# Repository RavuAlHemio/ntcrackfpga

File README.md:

# ntcrackfpga

FPGA-based NT hash cracker.

NT hashes are universally `MD4(UTF16LE(password))`. If you think this sounds like low-hanging fruit, that's because it is.

The reference implementation runs on a Lattice ECP5 Evaluation Board (`LFE5UM5G-85F-EVN`) while tests are simulated using Icarus Verilog. However, the Verilog code should be generic enough to work anywhere; device-specific settings are limited to `src/ntcrackfpga.lpf` and `src/clockdiv.v`.

See `PROTOCOL.md` on how to communicate with the cracker.

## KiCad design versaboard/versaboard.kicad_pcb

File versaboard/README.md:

# Versa Board

The cracker itself is structured to run on a Lattice ECP5 Evaluation Board (`LFE5UM5G-85F-EVN`; relevant settings may be found in `src/ntcrackfpga.lpf` and `src/clockdiv.v`). To provide a more convenient interface without attempting to implement I2C or UART in Verilog (and failing miserably), a Microchip-SAM-based _Versa Board_ solution is implemented, which is meant to mate directly with the Versa pins on the evaluation board.

The centerpoint of the _Versa Board_ is a Microchip (ex-Atmel) SAML21G18 microcontroller.

A KiCad hardware design is provided in this directory; the software implementation (in Rust) is in the `software` subdirectory.

## SAML21 pinout

The following SAML21 pins are used for the interconnection with the evaluation board:

| SAML21 pin | ECP5 Eval Board | function           | direction | ECP5 ball |
| ---------- | --------------- | ------------------ | --------- | --------- |
| PB08       | J39 pin 19      | `store_hash_byte`  | →         | A9        |
| PB09       | J39 pin 20      | `go`               | →         | B10       |
| PA06       | J39 pin 29      | `match_found`      | ←         | E7        |
| PA07       | J39 pin 31      | `your_turn`        | ←         | A11       |
| PA08       | J40 pin 4       | `new_hash_byte[0]` | →         | F1        |
| PA09       | J40 pin 6       | `new_hash_byte[1]` | →         | G1        |
| PA10       | J40 pin 8       | `new_hash_byte[2]` | →         | J5        |
| PA11       | J40 pin 10      | `new_hash_byte[3]` | →         | K3        |
| PA12       | J40 pin 12      | `new_hash_byte[4]` | →         | L5        |
| PA13       | J40 pin 14      | `new_hash_byte[5]` | →         | N5        |
| PA14       | J40 pin 16      | `new_hash_byte[6]` | →         | P5        |
| PA15       | J40 pin 18      | `new_hash_byte[7]` | →         | M3        |
| PA16       | J40 pin 1       | `output_byte[0]`   | ←         | K2        |
| PA17       | J40 pin 5       | `output_byte[1]`   | ←         | H2        |
| PA18       | J40 pin 7       | `output_byte[2]`   | ←         | J4        |
| PA19       | J40 pin 9       | `output_byte[3]`   | ←         | J3        |
| PA20       | J40 pin 11      | `output_byte[4]`   | ←         | L4        |
| PA21       | J40 pin 13      | `output_byte[5]`   | ←         | M4        |
| PA22       | J40 pin 15      | `output_byte[6]`   | ←         | N4        |
| PA23       | J40 pin 17      | `output_byte[7]`   | ←         | N3        |
| PA25       | J40 pin 21      | `step_active`      | →         | K5        |
| PB23       | J40 pin 23      | `step_clock`       | →         | M5        |
| PB22       | J40 pin 25      | `state_give`       | →         | L3        |
| PB10       | J40 pin 27      | for future use 0   | tbd       | N2        |
| PB11       | J40 pin 28      | for future use 1   | tbd       | M1        |
| PA27       | J40 pin 29      | for future use 2   | tbd       | L2        |

The following pins are used for other functions:

| SAML21 pin | function                              |
| ---------- | ------------------------------------- |
| PA00       | XIN32 (32kHz oscillator input)        |
| PA01       | reserved for XOUT32 (32k osc. output) |
| PA02       | GND to ensure oscillator stability    |
| PA03       | GND to ensure oscillator stability    |
| PA04       | UART TX (board to PC)                 |
| PA05       | UART RX (PC to board)                 |
| PA24       | on-board LED                          |
| PA30       | SWCLK (debugging, clock signal)       |
| PA31       | SWDIO (debugging, I/O)                |
| PB02       | GND to ensure oscillator stability    |
| PB03       | GND to ensure oscillator stability    |

## JLCPCB notes

If you wish to have this board manufactured by JLCPCB, please note the following rotation differences:

| components | description     | JLCPCB rotation        |
| ---------- | --------------- | ---------------------- |
| J1         | UART pins       | 90°                    |
| J4         | debug header    | 90°                    |
| J39, J40   | pin socket      | 270°                   |
| U1         | microcontroller | 270°? (to be verified) |

JLCPCB-specific rotations can be specified in the [KiCad JLCPCB Tools plugin](https://github.com/Bouni/kicad-jlcpcb-tools).

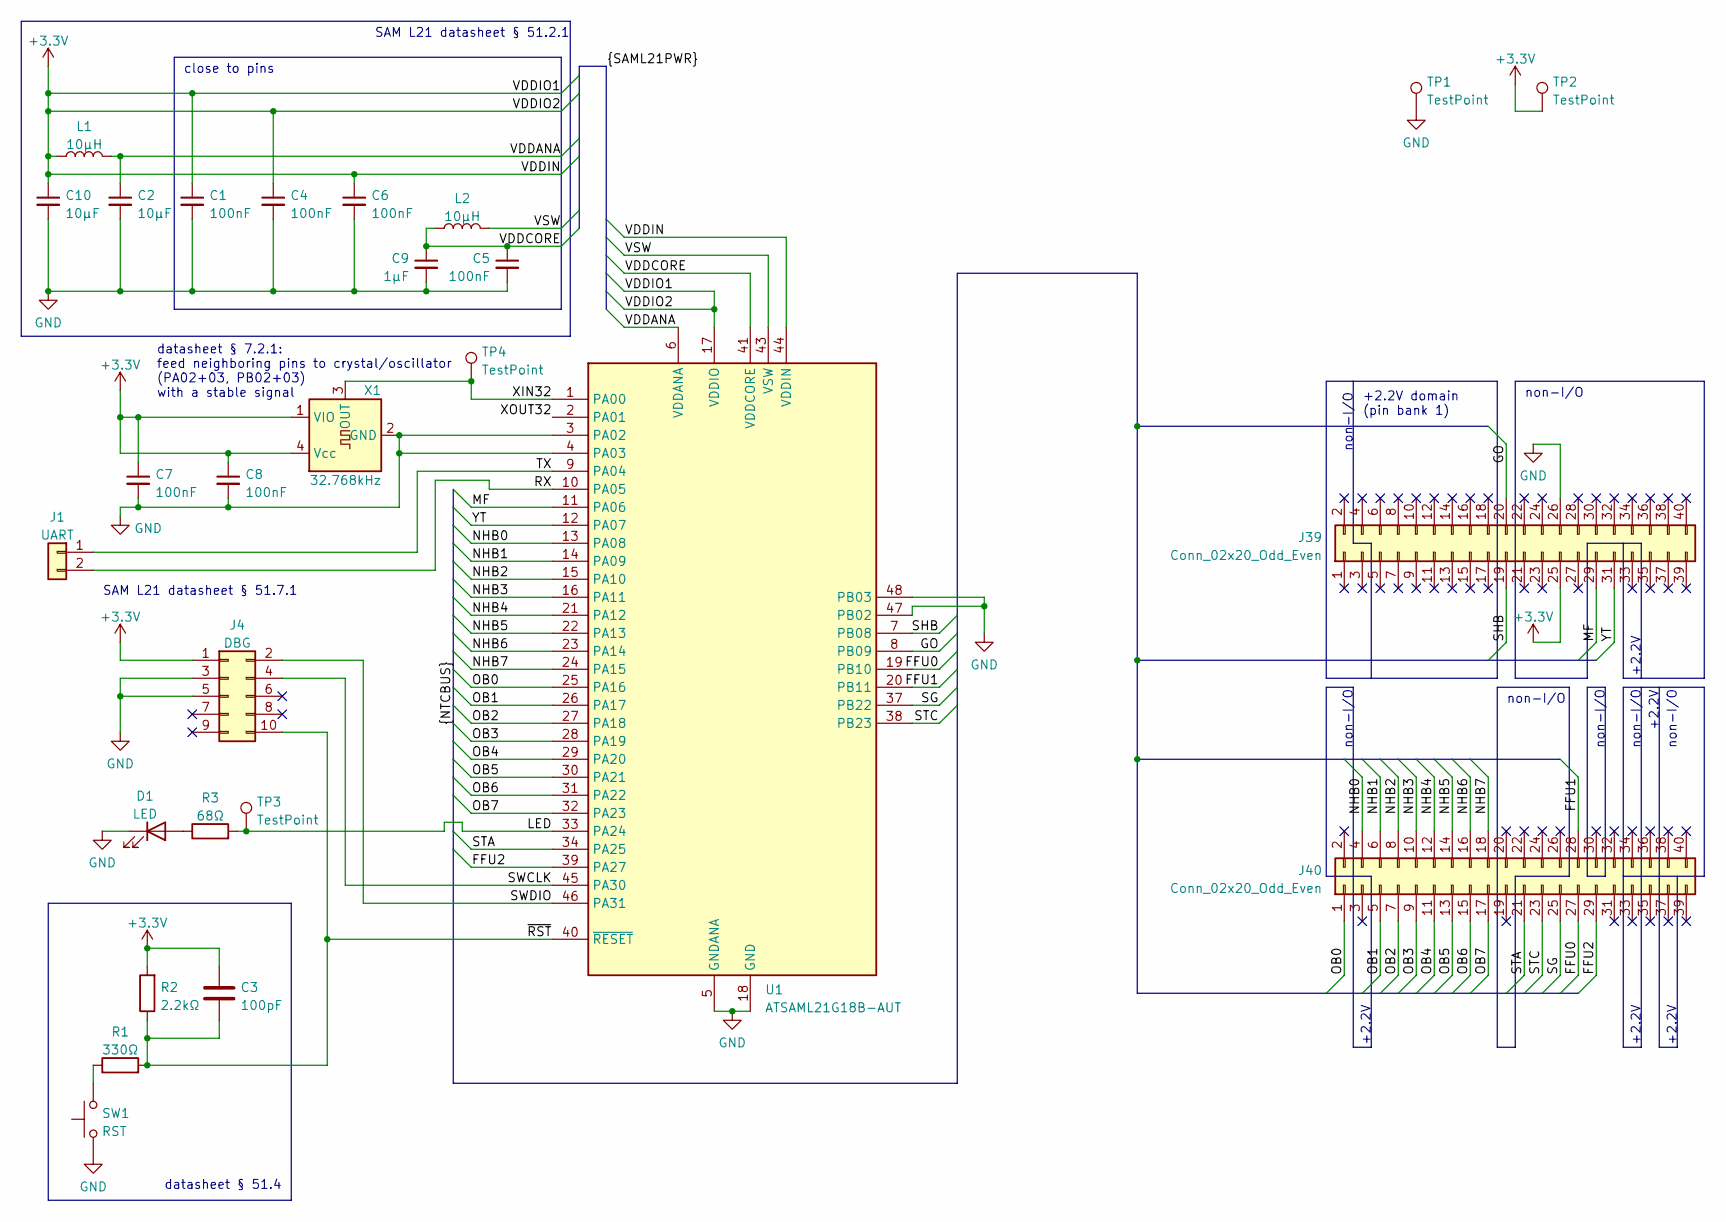
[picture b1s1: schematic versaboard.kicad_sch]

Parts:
C1, C4, C5, C6, C7, C8: 100nF; C_0402_1005Metric; JLCPCB C307331
C2, C10: 10µF; C_0603_1608Metric; JLCPCB C19702
C3: 100pF; C_0402_1005Metric; JLCPCB C1546
C9: 1µF; C_0402_1005Metric; JLCPCB C52923
D1: LED; LED_0603_1608Metric; JLCPCB C72038
J1: UART; Samtec_TSM-102-01-L-SH; JLCPCB C9900035116
J4: DBG; PinHeader_2x05_P1.27mm_Vertical_SMD; JLCPCB C5250218
J39, J40: Conn_02x20_Odd_Even; PinSocket_2x20_P2.54mm_Vertical_SMD; JLCPCB C2685111
L1, L2: 10µH; L_0603_1608Metric; JLCPCB C1035
R1: 330Ω; R_0402_1005Metric; JLCPCB C25104
R2: 2.2kΩ; R_0402_1005Metric; JLCPCB C25879
R3: 68Ω; R_0603_1608Metric; JLCPCB C27592
SW1: RST; Shou_Han_TS24CA; JLCPCB C393942
TP1, TP2, TP3, TP4: TestPoint; TestPoint_Pad_D1.0mm
U1: ATSAML21G18B-AUT; TQFP-48-1EP_7x7mm_P0.5mm_EP5x5mm_ThermalVias; JLCPCB C2052742
X1: 32.768kHz; Oscillator_SMD_SeikoEpson_SG3030CM; JLCPCB C2976104

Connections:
+3.3V: C1.1, C3.1, C4.1, C6.1, C7.1, C8.1, C10.1, J4.1, J39.25, L1.1, R2.2, TP2.1, U1.17 (VDDIO), U1.36 (VDDIO), U1.44 (VDDIN), X1.1 (VIO), X1.4 (Vcc)
/FFU0: J40.27, U1.19 (PB10)
/FFU1: J40.28, U1.20 (PB11)
/FFU2: J40.29, U1.39 (PA27)
/GO: J39.20, U1.8 (PB09)
/LED: R3.2, TP3.1, U1.33 (PA24)
/MF: J39.29, U1.11 (PA06)
/NHB0: J40.4, U1.13 (PA08)
/NHB1: J40.6, U1.14 (PA09)
/NHB2: J40.8, U1.15 (PA10)
/NHB3: J40.10, U1.16 (PA11)
/NHB4: J40.12, U1.21 (PA12)
/NHB5: J40.14, U1.22 (PA13)
/NHB6: J40.16, U1.23 (PA14)
/NHB7: J40.18, U1.24 (PA15)
/OB0: J40.1, U1.25 (PA16)
/OB1: J40.5, U1.26 (PA17)
/OB2: J40.7, U1.27 (PA18)
/OB3: J40.9, U1.28 (PA19)
/OB4: J40.11, U1.29 (PA20)
/OB5: J40.13, U1.30 (PA21)
/OB6: J40.15, U1.31 (PA22)
/OB7: J40.17, U1.32 (PA23)
/RX: J1.2, U1.10 (PA05)
/SG: J40.25, U1.37 (PB22)
/SHB: J39.19, U1.7 (PB08)
/STA: J40.21, U1.34 (PA25)
/STC: J40.23, U1.38 (PB23)
/SWCLK: J4.4, U1.45 (PA30)
/SWDIO: J4.2, U1.46 (PA31)
/TX: J1.1, U1.9 (PA04)
/VDDANA: C2.1, L1.2, U1.6 (VDDANA)
/VDDCORE: C5.1, C9.1, L2.1, U1.41 (VDDCORE)
/VSW: L2.2, U1.43 (VSW)
/XIN32: TP4.1, U1.1 (PA00), X1.3 (OUT)
/XOUT32: U1.2 (PA01)
/YT: J39.31, U1.12 (PA07)
/~RST: C3.2, J4.10, R1.2, R2.1, U1.40 (~RESET)
GND: C1.2, C2.2, C4.2, C5.2, C6.2, C7.2, C8.2, C9.2, C10.2, D1.1 (K), J4.3, J4.5, J39.26, SW1.1, TP1.1, U1.3 (PA02), U1.4 (PA03), U1.5 (GNDANA), U1.18 (GND), U1.35 (GND), U1.42 (GND), U1.47 (PB02), U1.48 (PB03), U1.49 (GND), X1.2 (GND)
unnamed: D1.2 (A), R3.1
unnamed: R1.1, SW1.2

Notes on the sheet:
SAM L21 datasheet § 51.7.1
datasheet § 51.4
+2.2V
SAM L21 datasheet § 51.2.1
non-I/O
close to pins
+2.2V domain (pin bank 1)
datasheet § 7.2.1: feed neighboring pins to crystal/oscillator (PA02+03, PB02+03) with a stable signal

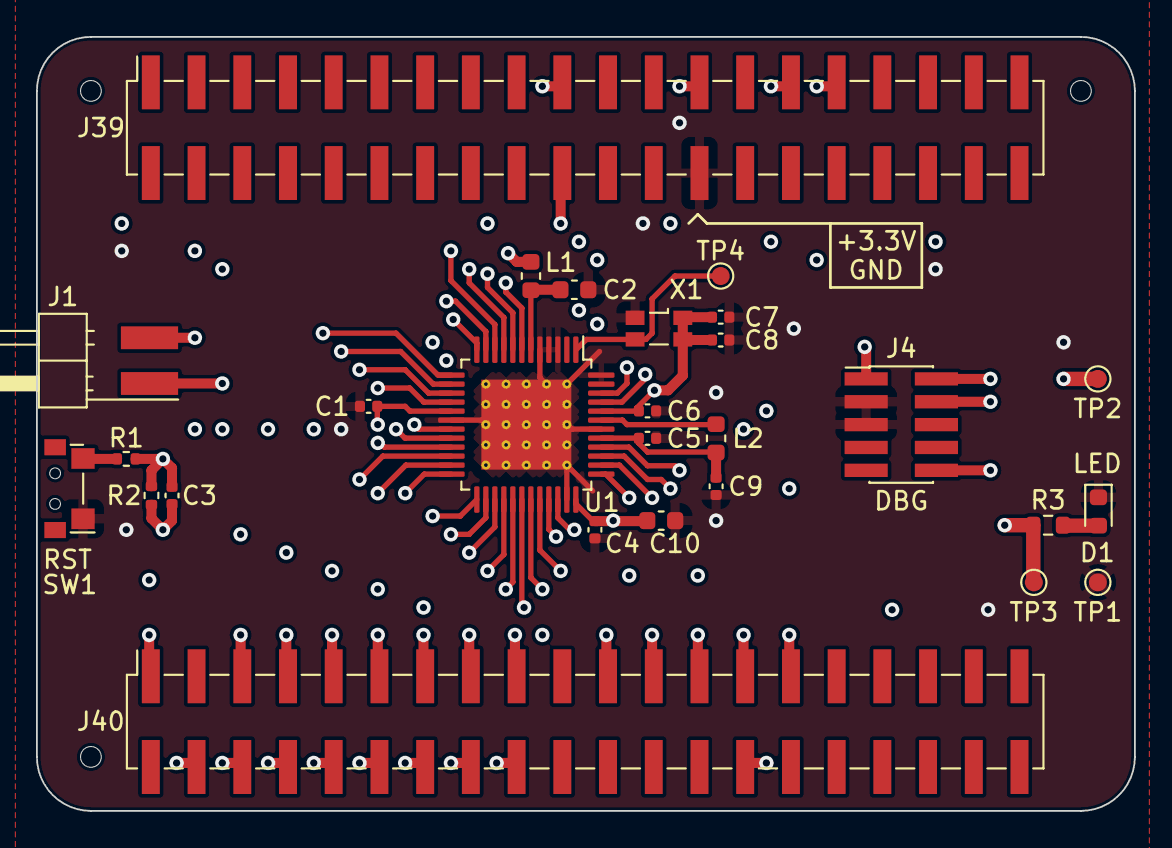
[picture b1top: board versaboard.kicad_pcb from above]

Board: 4 copper layers, 61.0 x 43.0 mm, 27 parts (0 on the bottom side), 40 nets.

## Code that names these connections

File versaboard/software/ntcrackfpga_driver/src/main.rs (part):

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        uart::send(&mut peripherals, b"\r\n");
    }

    // set PA24 (on-board LED) to output
    board_pin!(set_io, &mut peripherals, PA, 24);
    board_pin!(make_output, &mut peripherals, PA, 24);

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}

fn set_new_hash_byte(peripherals: &mut Peripherals, byte: u8) {
    // bit 0 = PA08, ... bit 7 = PA15
    const BIT_OFFSET: u32 = 8;

    let mut set_bits: u32 = 0;
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
#[inline]
fn get_output_byte(peripherals: &mut Peripherals) -> u8 {
    // bit 0 = PA16, ... bit 7 = PA23
    const BIT_OFFSET: u32 = 16;

    ((board_pin!(read_pins, peripherals, PA) >> BIT_OFFSET) & 0xFF).try_into().unwrap()
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
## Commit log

2022-10-31 remove clock modules; ECP5 clock pin must be imported at top level
2022-10-31 make MD4 calculation clock-driven
2022-10-31 make hashchecker clock-driven
2022-10-31 gen*.py: don't make index/length longer than necessary
2022-10-31 initial work on a password adder (incrementer)
2022-10-31 finish password incrementor, add a first test for it
2022-10-31 pwadder: rewrite muxing/demuxing using macros, finish unit tests
2022-10-31 fixes for hashchecker, tests
2022-10-31 MD4 block fixes, tests
2022-11-01 implement module where it all comes together
2022-11-02 genencode: reverse bytes, use jinja
2022-11-02 md4suck: add UTF-16LE modes to pad & ref
2022-11-02 md4block: ignore irdy during calculation
2022-11-02 ntcrackfpga: fix register sizes
2022-11-02 ntcrackfpga: fix number of password byte iterations
    frickin fencepost errors
2022-11-02 ntcrackfpga: add signal line "your turn"
2022-11-02 ntcrackfpga: disable dumpfile
    this is now handled from within the tests
2022-11-02 LPF: add "your turn" pin
2022-11-02 add integration test for the whole thing
2022-11-02 build.ninja: add generation of preprocessed files
2022-11-03 divide the clock
    200 MHz is too fast
2022-11-03 clockdiv=1 on simulations
2022-11-03 transmit password length after password
2022-11-03 annotate LPF
2022-11-03 add README, document communication protocol
2022-11-03 initial commit of driverboard code (WIP)
2022-11-04 driverboard: init routine
2022-11-04 driverboard: initial work on UART setup
2022-11-04 driverboard: UART setup code
2022-11-06 driverboard: uart: remove interrupt handler
    Let the application crate handle UART "byte received" interrupts.
2022-11-06 driverboard: uart: read-modify-write
2022-11-06 driverboard: uart: general TLC
2022-11-06 driverboard: pin: fix set_high/set_low implementations
2022-11-06 driverboard: pin: add inline hint
2022-11-06 driverboard: add i2c module (host/master only)
2022-11-06 driverboard: (very) initial work on app crate
2022-11-06 driverboard: use linker script
2022-11-06 driverboard: fix UART setup
2022-11-06 driverboard: also activate SERCOM interrupts centrally
2022-11-06 driverboard: add UART interrupt handler utilities
2022-11-06 driverboard: make device crate optionally depend on critical-section
2022-11-06 driverboard: fix board_pin! code for make_input and make_output
2022-11-06 driverboard: add memory layout definitions
2022-11-06 driverboard: add dependencies, UART decoder
2022-11-06 driverboard: add build scripts
2022-11-06 driverboard: ignore .bin file
2022-11-07 driverboard uart: early return sending 0 bytes
2022-11-07 driverboard build: shorten size output
2022-11-07 driverboard: critical-section byte buffer copy
2022-11-07 driverboard: implement control logic
2022-11-07 clkdiv: use on-board clock dividers
2022-11-08 third clock division
2022-11-08 build.ninja: remove absolute tool paths
2022-11-08 CI/CD: add workflow
2022-11-08 CI/CD: fix runner.arch syntax
2022-11-08 CI/CD: move "if" out of "with"
2022-11-08 CI/CD: quote architecture
2022-11-08 CI/CD: strings are single-quoted
2022-11-08 CI/CD: fix build command
2022-11-08 CI/CD: fixes
2022-11-08 ntcrackfpga: also run main module on div_clk
2022-11-08 clockdiv: only divide once by 3.5
2022-11-13 add custom driver board "versaboard" design
2022-11-13 driverboard: allow choosing debug over release build
2022-11-13 driverboard: add OpenOCD config for debugging
2022-11-13 versaboard: geographic reannotate
2022-11-13 versaboard: add LCSC numbers
2022-11-13 versaboard: show µC model number
2022-11-13 move Arduino Zero driverboard aside
    the Versaboard design is no longer an I2C muxer but a specialized µC board
2022-11-14 add ATSAML21G18B SVD file for versaboard
2022-11-14 versasw: remove invalid enumerated values from ATSAML21G18B SVD
    GCLK.SYNCBUSY.GENCTRLx are each only 1 bit wide; it is rather unlikely that
    they can house a 9-bit-wide bitflag GCLKx.
2022-11-14 versaboard sw: add WIP implementation
2022-11-14 CI/CD: build Versaboard software
2022-11-14 CI/CD: update path to Arduino Zero driver board
2022-11-14 versaboard sw: pin and uart: SAMD21 -> SAML21
2022-11-14 versaboard sw: allow targeting multiple pins simultaneously
2022-11-14 versaboard sw: basic pin setup
2022-11-14 versaboard sw: multi-pin macros, part 2
2022-11-14 versaboard sw: uart: use multipin feature
2022-11-14 versaboard sw: fix incorrect state check
2022-11-14 versaboard sw: convert from I2C to direct pinning
2022-11-14 versaboard: add JLCPCB mounting holes
2022-12-07 versaboard: add some text
2022-12-07 versaboard: increase UART arrow sizes
2022-12-07 versaboard: note JLCPCB-specific rotations in the README
2022-12-08 versaboard r0002: replace crystal with oscillator, add test points
    the crystal on the test run of r0001 does not stabilize; switch to an
    oscillator which should manage this without our support
    also add a few test points on the board
2022-12-21 versaboard sw: switch to PL2 before clock setup
2022-12-22 versaboard sw: document clock topology as diagram
2022-12-22 versaboard sw: always run XOSC32K, not just on demand
    this is the reason XOSC32K never stabilized
2022-12-22 versaboard sw uart: configure the correct clock
    clock 17 is the slow clock for SERCOM0 through SERCOM4; we want clock 18,
    which is the core clock for SERCOM0
2022-12-22 versaboard sw: fix copying byte buffer
    we need to copy the whole bytes array, not just the currently-valid slice,
    or copy_from_slice panics
2022-12-22 versaboard sw: more talkative panic handling
    we have UART now; use it
2022-12-22 versaboard sw: fix carriage return detection
    it's 0x0D, not 0x0C
2022-12-22 versaboard sw: hex-dump unexpected control characters on USART input
2022-12-22 versaboard sw: add "p" command to output pin status
2022-12-23 versaboard r0003: avoid FPGA pin bank 1
    Pin bank 1 on the ECP5 evaluation board is +2.5V by default and this can
    only be changed by resoldering SMD resistors. Yeah, no.
2022-12-23 versaboard versabanks: make differing voltage bold
2022-12-23 change VersaBoard pinout (LPF)
    The reasoning behind this pinout is documented in
    versaboard/versabanks.md
2022-12-24 versaboard sw: also accept DEL as backspace
2022-12-24 build: actually feed the LPF to nextpnr_ecp5
2022-12-24 build: don't capture yosys and nextpnr console output, let it flow
    this is done by using the ninja pool "console"
2022-12-24 hw: can't use Y19 for clock; use OSCG instead
2022-12-24 output to a blinky LED to see that things are progressing
2022-12-24 versaboard: add r0002-to-r0003 pinout diagram
    useful for connecting a r0002 board to an ECP5 Evaluation Board
    programmed with a r0003 bitstream
2022-12-24 versaboard sw: enable reading circuitry for input pins
    apparently PINCFG.INEN must be set as well; DIR is not enough
2022-12-24 versaboard sw: improve cmdline lecture
2022-12-24 versaboard sw: homogenize post-cmdline-lecture behavior
2022-12-25 integration test: mention blinky LED
2022-12-25 integration test: bind to correct clock
2022-12-25 integration test: allow for early breakout
2022-12-25 blinky LED: show bottom bit of password
2022-12-25 versaboard sw: default state is Unknown
2022-12-25 versaboard sw: only wait for interrupt if the µC can remain passive
2022-12-25 try clock divisor 8 instead of 5
2022-12-25 implement single-step operation & current-state dumping
2022-12-26 fix debounce parameter base
2022-12-26 versaboard: add STA, STC and SG pins
2022-12-26 state_giver: only output first two hashes
    placement takes forever otherwise
2022-12-26 state_giver: also output state registers
2022-12-26 versaboard README: password_byte became output_byte
2022-12-26 versaboard README: document step_(active|clock) and state_give
2022-12-26 versaboard README: update other functions table
2022-12-26 versaboard: lead more pins to J40 for potential future use
2022-12-26 versaboard sw: password byte is now output byte
    it is also used for state output in state-output mode
2022-12-26 versaboard sw: improve output byte output on "p"
    order bits correctly (MSB-first), also output in hex and, for printable
    characters, as character
2022-12-26 versaboard sw: don't deactivate LED on first SERCOM0 interrupt
    we no longer need this debug functionality now that we got UART to work
2022-12-26 versaboard sw: reverse order of hash transmission to FPGA
    it expects the bytes in little-endian order
2022-12-26 versaboard sw: sleep a bit before pulling "store_hash_byte" high
    let the bits settle a bit
2022-12-26 versaboard sw: make crystal vs. oscillator a compile-time option
    specify the cargo package feature "crystal" to get crystal behavior; don't
    specify it to get oscillator behavior
2022-12-26 mention DIP switch silkscreen erratum in LPF
2022-12-26 versaboard sw: fix character index in string template
2022-12-26 state_giver: intercalate data markers
2022-12-26 state_giver: annotate each section with byte count
2022-12-26 ntcrackfpga: wait for external flags to be lowered
    otherwise we might run through multiple phases of the process because
    our clock and the caller's clock are not in sync
2022-12-27 md4block: wait for irdy to be raised *and* lowered
2022-12-27 ntcrackfpga: fix go detection, ensure termination
2022-12-27 ntcrackfpga_hw: speed up the clock (DIV=8 -> DIV=5)
2022-12-27 versaboard sw uart: allow sending slices
2022-12-27 versaboard sw: fix off-by-one error when receiving passwords
2022-12-27 versaboard sw: handle password being transmitted in reverse
2022-12-29 implement a reset signal
2022-12-29 build: place harder
2022-12-29 fewer hashes (otherwise the placer doesn't manage)
